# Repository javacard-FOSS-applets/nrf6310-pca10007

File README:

ZMMMMMMMMMMMMMMMMMMMMMMMMMMMMMMMMMMMMMMMMMMMMM?       
    .MMMMMDDDDDDDDDDDDDDDDDDDDDDDDDDDDDDDDDDDDDDDDMMMM      
   ZMMMM..                                         MMMMM    
..MMMM 8MMMMMMD.                             MM     ZMMMM?  
MMMMM  MMMNNMMMMMM                          MMMM      MMMMM 
MMM:   MMD      MMO                        +MMMM=       MMMM
MMD    MMD      MMD                        MM  MM       NMMN
MMD    MMD     DMM                        MM?  ?MM      NMMN
MMD    MMMMMMMMMM     ...        .7       MM    MM      MMMN
MMD    MMD          . ,         . 87.    MMMMMMMMMM     MMMN
MMD    MMD         . 7          . ~M    MMM      MMM    MMMN
MMD    MMD           M          .. M.   MM        MM    MMMN
MMD    MM8         ..N ..        .MM.  MNM        MMM   MMMN
MMD                ..+I  ...      M..                   MMMN
MMD                .. M.. MMMM? .,M..                   MMMN
MMD                   MN MMMMMM?IM..~                   MMMN
MMD                .  .MMMMMMMMMM:MM                    MMMN
MMD                7MMMMZIMMMMMMM+. ..                  MMMN
MMD                  .  OMMMMMMZ    .                   MMMN
MMD                  ..:MMMMMMMMMMMM..                  MMMN
MMD                 .ZMMMMMOMMMOMM 7O                   MMMN
MMD         .MMM    .MIMD MII~7 .8M8M?                  MMMN
MMD         MMM      MMZ        . ?M.M .                MMMN
MMD         ..      7MMD        ..~M..7.                MMMN
MMD    NM8      NN8 ?M M          =M    MMM~      MM    MMMN
MMD    MM8      MM8  . ,7         MI      MMM     MM    MMMN
MMD    MMD      MMD      8                 +MM:   MM    MMMN
MMD    MMD      MMD                          MMM  MM    MMMN
MMD    MMD      MMD                          .MMMMMM    MMMN
MMD    MMN      MMD                         OMM+MMMM    MMMN
MMD    8MN      MMD                        OMM    MM    MMMN
MMM+    MM      MM.                       MMM     MM    MMMN
MMMMM.  DMMMMMMMMD                       MMM      MM. MMMMM 
  MMMM?   ,ID8I                        .7I7       MM MMMM+  
   ?MMMM.                                          MMMMM    
     MMMMMMMNNNNNNNNNNNNNNNNNNNNNNNNNNNNNNNNNNNNMMMMMM      
     ?MMMMMMMMMMMMMMMMMMMMMMMMMMMMMMMMMMMMMMMMMMMMM+.       
        NMMMMMMMMMMMMMMMMMMMMMMMMMMMMMMMMMMMMMMMMMM  

Requirements:
	HW
		
	SW

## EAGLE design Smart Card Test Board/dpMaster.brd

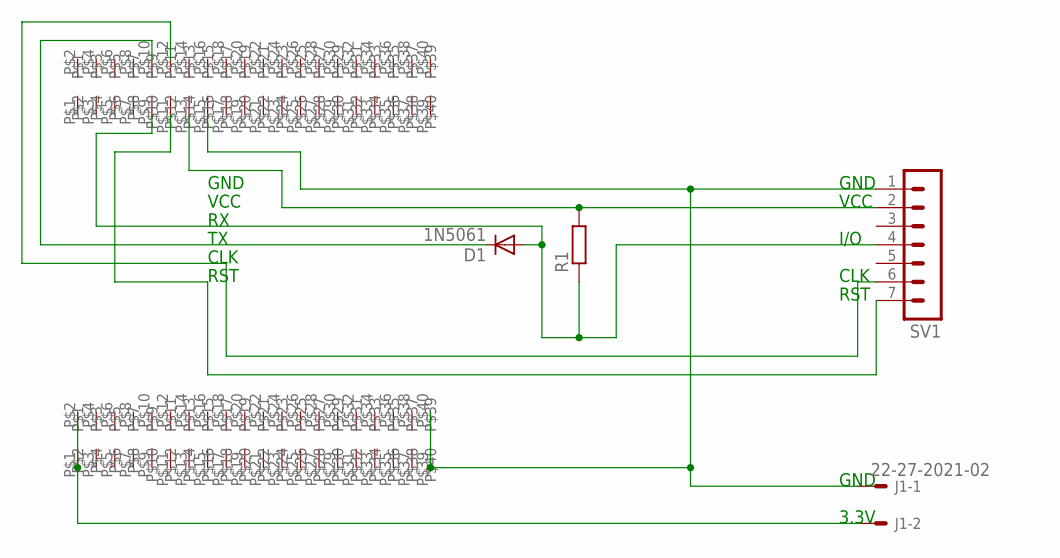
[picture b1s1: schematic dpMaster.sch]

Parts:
D1: 1N5061; SOD57-10
J1: 22-27-2021-02; 6410-02
R1: R-EU_0207/12; 0207/12
SV1: MA07-1
U$1, U$2: SFC-120-T2-L-D

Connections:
unnamed: D1.C, U$1.P$10
unnamed: SV1.6, U$1.P$12
unnamed 2: J1.2, U$2.P$1, U$2.P$2; also elsewhere on the board
unnamed: D1.A, R1.1, SV1.4, U$1.P$9
unnamed: SV1.7, U$1.P$11
unnamed: R1.2, SV1.2, U$1.P$13
unnamed 6: J1.1, SV1.1, U$1.P$15, U$2.P$39, U$2.P$40; also elsewhere on the board

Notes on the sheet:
GND
VCC
CLK
RST
I/O
3.3V

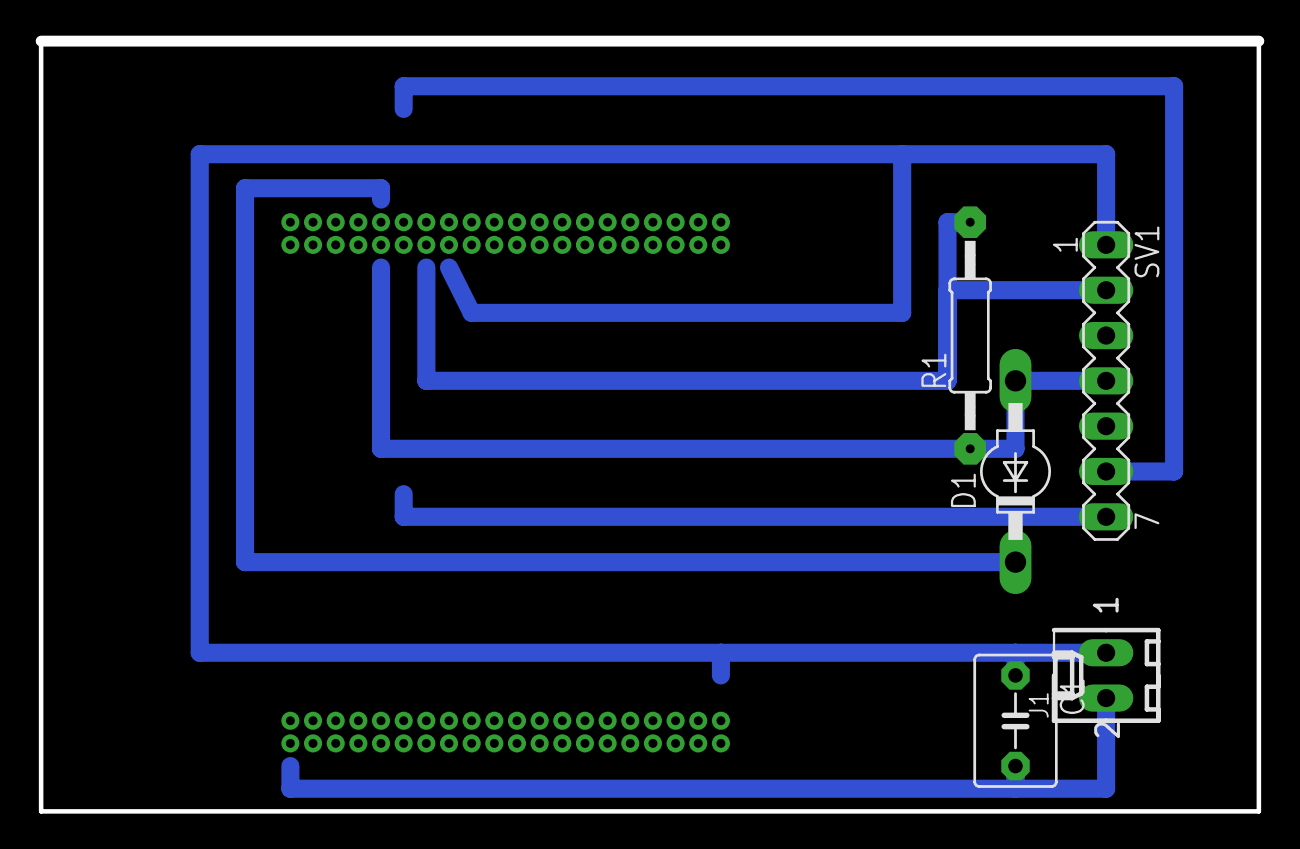
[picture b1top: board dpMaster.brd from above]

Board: 2 copper layers, 68.2 x 43.0 mm, 7 parts (0 on the bottom side), 7 nets.

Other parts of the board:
C1: C5B4.5

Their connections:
unnamed 2: C1.2; also elsewhere on the board
unnamed 6: C1.1; also elsewhere on the board

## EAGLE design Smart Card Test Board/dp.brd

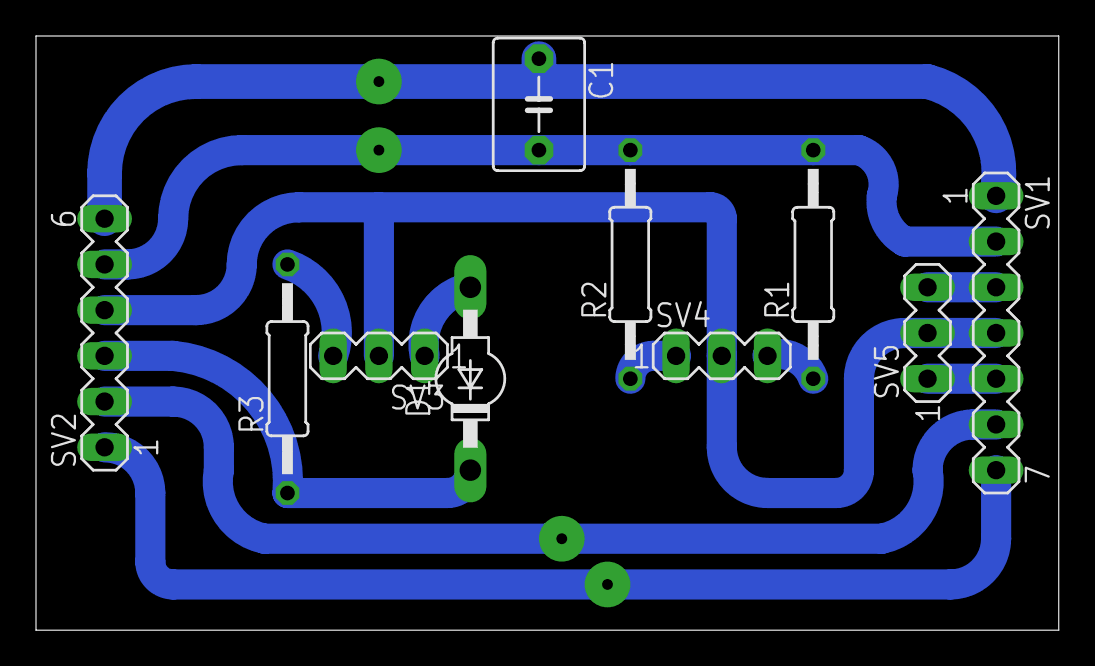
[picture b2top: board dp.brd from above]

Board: 2 copper layers, 56.8 x 33.0 mm, 10 parts (0 on the bottom side), 12 nets.

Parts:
C1: C5B5
D1: 1N5061; SOD57-10
R1, R2, R3: 0207/12
SV1: MA07-1
SV2: MA06-1
SV3, SV4, SV5: MA03-1

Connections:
unnamed: C1.2, R1.2, R2.2, SV1.2, SV2.5
unnamed: C1.1, SV1.1, SV2.6
unnamed: SV1.7, SV2.1
unnamed: SV1.6, SV2.2
unnamed: D1.C, R3.1, SV2.3
unnamed: SV1.4, SV2.4, SV3.2, SV4.2, SV5.2
unnamed: R3.2, SV3.3
unnamed: D1.A, SV3.1
unnamed: R2.1, SV4.1
unnamed: R1.1, SV4.3
unnamed: SV1.3, SV5.3
unnamed: SV1.5, SV5.1

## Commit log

2016-11-27 Third iteration of software
    No functioning MBR at 0xFFFFFFFE, LEDS test with buttons input test, RTT
    debug console test
    For keil 5.21.1.0
2016-11-27 Vypis zmeny na tlacidlach na RTT
2016-11-28 LEDs port test with buttons
2016-11-28 Improved PreparedLEDS method
2016-11-28 Dorobene citanie teploty
    TODO use nrf_temp.h
    -teplota je 10 bitova hodnota, potrebne previest potom na uint32_t
2016-12-02 Order of build has changed
    *Order of build has changed
    *Second target added, not workiong yet
2016-12-04 Temperature condition wait change
2016-12-04 Temperature reading fix
2016-12-13 Document added
2017-03-12 It communicates
    Sends buttton presses from master to slave back to master && draws them
    on the leds
2017-03-16 Segmentacia predpriprava
    predpriprava segmentacie vacsej spravy ako 8 bytov cez broadcast
2017-03-17 Master posiela segmentovane data
2017-03-17 Both sides uses segmenter for recieve && transmit
2017-03-20 Preparation for encryption && decryption
    Added encrypt decrypt cababilities, tested new program layout
2017-03-20 Project cleanup
2017-03-23 Added AES SW support using TinyAES128 C
    libtomcrypt missing tommath.h
    libssl too complex && for unix config make make install
    cryptocpp for CPP obviosly, not usable in c
    libgcrypt not anayled deeply
2017-03-24 SW AES Used working stable
2017-03-27 Everything important is in current directory
2017-03-30 JC Applet preparation
    for windows && eclispse
    with automated test in eclipse
2017-03-31 JC Applet Dummy APDU && responses Finished
    with tests at first glance, seemed to be working,
    needs refurbishing though
2017-03-31 Applet code cleaned
2017-04-01 3.5 MHz CLK preparation && project cleanup
    Need to calculate CLK to be as close to 3.5 MHz
2017-04-01 Cleanup II
2017-04-02 UART recieve,send WORKS
    it comuniacates
    -TX pin 0, port0
    -RX pin 1, port0
    -connect to header P15
    todo timeout after send, for 400 - 40 000 cycles of CLK
    Master Slave, always going to send first, than wait for response
2017-04-02 JC Added functionality for AES enc/dec
    Not tested on real hardware, in sim returns 0x0003 No Such ALGORITHM
2017-04-03 CLK generation tested on pin 7
    4MHz 2.78, 1,
2017-04-03 Part II
2017-04-03 Reset pin for iso 7816 && cleanup
2017-04-07 ISO7816 functions preparation
2017-04-08 ISO 7816 init and warm reset
2017-04-08 ATR recieved
    -custom baudrate 7467
    -recieved
    3B EA 00 00 81 31 FE 45 00 31 C1 73 C8 40 00 00 90 00 7A
    3B F8 13 00 00 81 31 FR 45 4A 43 4F 50 76 32 34 31 B7
2017-04-08 Fixe problem with writing to GPIO affected other pins && added timeout to UART
2017-04-08 Debug info added through SeggerRTT
2017-04-09 Send APDU && get response test
2017-04-10 UART on one GPIO pin does not work
    need to put TX andd RX to different pins && connect them externaly
2017-04-10 UART cleaned up, configed it to two GPIO pins
    https://devzone.nordicsemi.com/question/127396/is-it-physically-possible-to-set-uart-rx-and-tx-to-same-gpio-pin/
2017-04-11 7816 Trying to negotiate t=0
    -bug with UART, after inicialization, send about 2 character 0x00 &&
    0xff
    -one wire UART might not be working properly, need DOSC to analyze
    further
2017-04-11 Clean up?
2017-04-12 ISO 7816 UART one wire NO WORKY WORKY
    tried:
    -passive tx 10k rx
    -passive rx diode tx
    -with and withou pull-up 10k 4.7k
    -still no response from the cryptoelement
    PTS no response 0xFF 0x00 0xFF
2017-04-13 Clean-up, buttonwait, proper UART disable
    -Clean-up of the 7816.c
    -after init waiting for the button press
    -UART proper disable, Smart card was beeing power throu IO pin
2017-04-13 YEEEAHHHA: Finaly got response from Crypto element
    -T=0 communications not worky worky
    -PST negotiation no worky worky
    -T=1 communication GOT RESPONSE!
2017-04-15 ISO7816 operations for different messages added
2017-04-17 ISO 7816: Message checking - NOT TESTED
2017-04-17 Project info added
2017-04-17 ISO7816 message integrity checks (basic)
2017-04-18 ISO7816: Basic ATR message parsing (REALY CRUDE and RAW)
2017-04-19 ISO7816 Standard APDU errors messages
    +trying to locate Card manager
2017-04-19 ISO7816 more erros from another source
2017-04-20 ISO7816 clean up
2017-04-20 ISO7816 Segger converter+clean up
2017-04-20 ISO7816 some progress
    Tested Segger to ISO7816
    Connected SIM card through APDU's (0x3bh 0x9eh 0x96h 0x80h 0x1fh 0xc7h
    0x80h 0x31h 0xe0h 0x73h 0xfeh 0x21h 0x1bh 0x66h 0xd0h 0x01h 0x7bh 0x10h
    0x0fh 0x00h 0x65h)
    Tryed to fix ocaisional CLK stop stuck at ONE, not zero
2017-04-20 Info about T-mobile SIM ATR
2017-04-21 UART to ISO7816 Test Dev Board
    Tested
2017-04-24 ISO7816 converter progress
    Added Bruteforcing location of Classes, Instructions, Card Manager
2017-04-24 ISO7816 converter cleanup
2017-04-24 ISO7816 Message checks corrected
2017-04-24 ISO7816 converter progress
2017-04-25 ISO7816 UART minor change
2017-04-26 ISO7816 TPDU send bit toggling
2017-04-26 ISO7816: Try CPCLD , try Get Record
2017-04-26 ISO7816: INS references added
2017-04-26 ISO7816 more depth
2017-04-26 ISO7816: Timing functions
2017-04-27 ISO7816: still buildable in evaluation mode
2017-04-27 ISO7816: T=1, timing reverse engenering preparation
    for connecting to PS/CS pin IO
2017-04-28 ISO7816: Parity control ON/OFF
2017-04-28 ISO7816: clean up
2017-04-29 ISO7816: progress
    todo: try to put LRC at the end of the APDU in the BLOCK in T=1
2017-04-29 ISO7816: Bits and pieces
2017-04-29 ISO7816: Big BLOB of everything, clean up mostly, BUT
    managed to get reasonable response from cyptoelement
2017-04-29 ISO7816: Added some responses, need to analyze them though
2017-04-30 ISO7816: around applet methods, NOT TESTED, but buildable
2017-04-30 ISO7816: Communication with Helloworld applet test with cryptoelement
2017-04-30 Trying to install applet via PS/CS reader and GPShell
2017-05-01 ISO7816: Preparation methods for sending data to encrypt and decrypt via SC
2017-05-01 Trying to install compiled cap file to java card
2017-05-02 Tryin to install applet part 2
2017-05-03 Installation of applet succesfull
2017-05-03 Compatibility test
2017-05-03 Just trying
2017-05-03 Applet for Eclipse35 JC222 JCDE JRE160
2017-05-03 Preparation for RSA applet crypto
2017-05-03 Debugging session
2017-05-03 Second UART-ISO7816 board for Slave
2017-05-03 sfc-120-t2-l-d lib for eagle
2017-05-03 Functioning applet for NXP JC222 and my UART-ISO
2017-05-03 ISO7816: Small clean up
2017-05-04 Install scripts for GPShell
2017-05-04 Board v3
2017-05-04 CLK: Test for CLK generation tidy up
2017-05-05 MASTER: Bootloader added
2017-05-05 KEILu4: Saving space on RO-data to fit 32kB limit
2017-05-05 Clean up
    Clean up
    Globals
    Bootloader progress
2017-05-05 Bootloader: ISO debuge tested
2017-05-05 Quick fix of somehow changed value
2017-05-05 HUGEEE clean up
2017-05-05 HW_AES debugging
2017-05-05 ANT Resync, after ISO7816 communication
    After communication with ISO7816, desync of ANT protocol happens.
    Communication takes place over multiple TX events, some recieved events
    are lost.
2017-05-05 Segmenter: Resync changed
2017-05-05 Verificaition: automated test added
    master will automaticly send data till MAX, if recieves value wich he
    sent to slave back, goes to next data
2017-05-05 Validation: auto test end signalisation
    leds will blink in very specific way
2017-05-06 DOC: Obrazky
2017-05-06 Doc bib tex
2017-05-06 Keil
2017-05-06 Applet update
2017-05-06 Cap update
2017-05-07 Keil: added defines, to get MEMORY requirements
2017-05-09 Applet: variable name fix
2017-05-09 Keil: Automated test personalization
2017-05-09 Keil: Test fix
2017-05-10 Doc: zhodnotenie fazy
2017-05-10 Doc fix
2017-05-10 Doc: Going to sleep...
2017-05-10 Doc: almost final
2017-05-10 Doc: spelling
2017-05-10 Doc: A4 format
2017-05-10 Doc pdf
2017-05-10 Doc: overflow fix
2017-05-10 Doc:
2017-05-11 Doc: Final
2017-05-14 JC: RND data function added
    byte 0x52 in data return 1 byte of random data
2017-05-14 JC: playing with RSA
2017-05-14 JC: RSA functioning encryption/decryption
2017-05-14 JC: plain text encode/decode does something, but not works
    The change of RSA cipher does not work
2017-05-21 JC: RSA init in specific APDU
    so that selecting applet does not take 10 s because of generating RSA
    keypair
2017-05-21 JC: JC222 supports nativly only ECDSA
    no ECC... search for Elliptic Curve Integrated Encryption Scheme
2017-06-03 JC: ATR message from some card
2017-06-12 Presentation: added
2017-06-12 Presentation: Defense Cont.
2017-06-12 Presentetaion: Defense Cont.
2017-06-13 Presentation: Defense. Cont.
2017-06-13 Presentation: Final
